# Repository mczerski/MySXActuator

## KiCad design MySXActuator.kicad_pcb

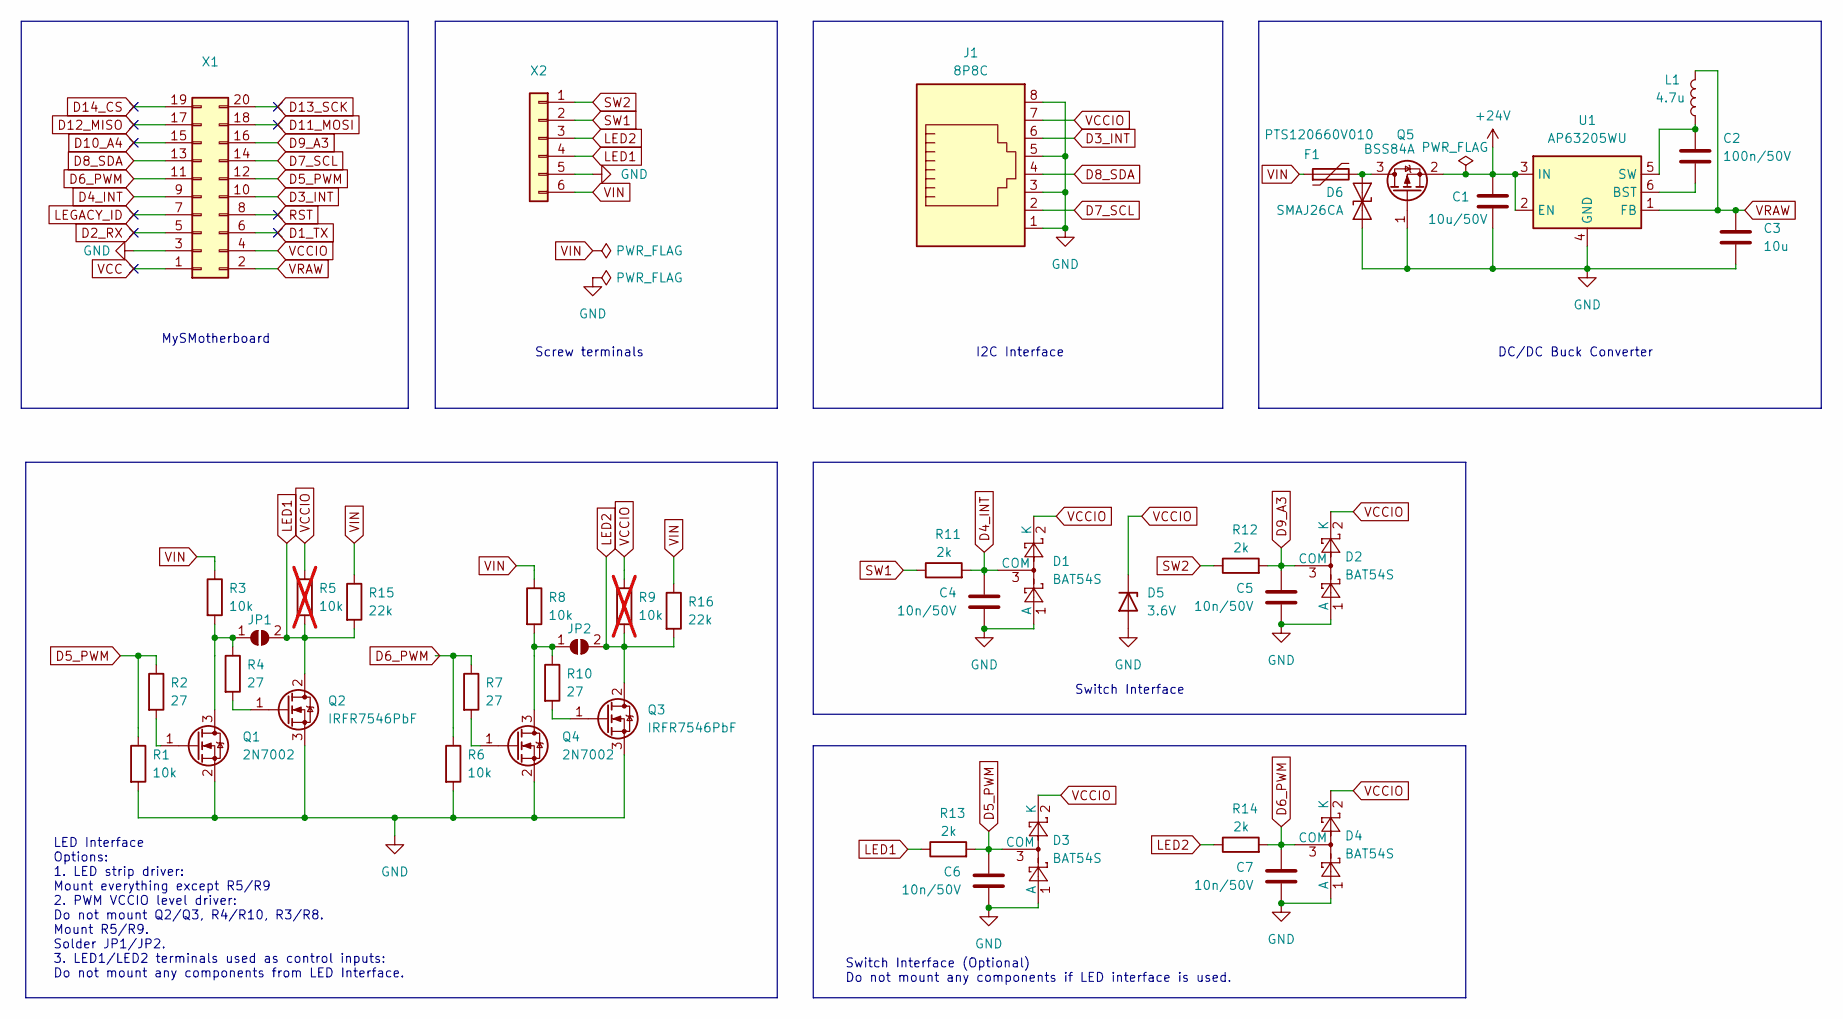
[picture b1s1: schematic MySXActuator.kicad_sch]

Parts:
C1: 10u/50V; C_1206_3216Metric
C2: 100n/50V; C_0402_1005Metric_Pad0.74x0.62mm_HandSolder
C3: 10u; C_1206_3216Metric
C4, C5, C6, C7: 10n/50V; C_0402_1005Metric
D1, D2, D3, D4: BAT54S; SOT-23
D5: 3.6V; D_MiniMELF
D6: SMAJ26CA; D_SMA
F1: PTS120660V010; Fuse_1206_3216Metric_Pad1.42x1.75mm_HandSolder
J1: 8P8C; AMPHENOL_54601-908WPLF
JP1, JP2: SolderJumper-2_P1.3mm_Open_RoundedPad1.0x1.5mm
L1: 4.7u; L_1210_3225Metric
Q1, Q4: 2N7002; SOT-23
Q2, Q3: IRFR7546PbF; TO-252-2
Q5: BSS84A; SOT-23
R1, R3, R6, R8: 10k; R_0603_1608Metric
R2, R4, R7, R10: 27; R_0603_1608Metric
R5, R9: 10k; R_0603_1608Metric; not fitted
R11, R12, R13, R14: 2k; R_0603_1608Metric
R15, R16: 22k; R_0603_1608Metric
U1: AP63205WU; TSOT-23-6
X1: FE10-2
X2: TerminalBlock_Phoenix_MKDS-1,5-6-5.08_1x06_P5.08mm_Horizont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

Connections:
+24V: C1.1, Q5.2 (S), U1.2 (EN), U1.3 (IN)
D1_TX: X1.6
D2_RX: X1.5
D3_INT: J1.6, X1.10
D4_INT: C4.1, D1.3 (COM), R11.2, X1.9
D5_PWM: C6.1, D3.3 (COM), R1.1, R2.1, R13.2, X1.12
D6_PWM: C7.1, D4.3 (COM), R6.1, R7.1, R14.2, X1.11
D7_SCL: J1.2, X1.14
D8_SDA: J1.4, X1.13
D9_A3: C5.1, D2.3 (COM), R12.2, X1.16
D10_A4: X1.15
D11_MOSI: X1.18
D12_MISO: X1.17
D13_SCK: X1.20
D14_CS: X1.19
GND: C1.2, C3.2, C4.2, C5.2, C6.2, C7.2, D1.1 (A), D2.1 (A), D3.1 (A), D4.1 (A), D5.2 (A), D6.1 (A1), J1.1, J1.3, J1.5, J1.8, Q1.2 (S), Q2.3 (S), Q3.3 (S), Q4.2 (S), Q5.1 (G), R1.2, R6.2, U1.4 (GND), X1.3, X2.5
LED1: JP1.2 (B), Q2.2 (D), R5.2, R13.1, R15.2, X2.4
LED2: JP2.2 (B), Q3.2 (D), R9.2, R14.1, R16.2, X2.3
LEGACY_ID: X1.7
unnamed: D6.2 (A2), F1.2, Q5.3 (D)
unnamed: JP1.1 (A), Q1.3 (D), R3.2, R4.1
unnamed: JP2.1 (A), Q4.3 (D), R8.2, R10.1
unnamed: Q1.1 (G), R2.2
unnamed: Q2.1 (G), R4.2
unnamed: Q3.1 (G), R10.2
unnamed: Q4.1 (G), R7.2
unnamed: C2.1, U1.6 (BST)
unnamed: C2.2, L1.1, U1.5 (SW)
RST: X1.8
SW1: R11.1, X2.2
SW2: R12.1, X2.1
VCC: X1.1
VCCIO: D1.2 (K), D2.2 (K), D3.2 (K), D4.2 (K), D5.1 (K), J1.7, R5.1, R9.1, X1.4
VIN: F1.1, R3.1, R8.1, R15.1, R16.1, X2.6
VRAW: C3.1, L1.2, U1.1 (FB), X1.2

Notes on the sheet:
I2C Interface
LED Interface Options: 1. LED strip driver: Mount everything except R5/R9 2. PWM VCCIO level driver: Do not mount Q2/Q3, R4/R10, R3/R8. Mount R5/R9. Solder JP1/JP2. 3. LED1/LED2 terminals used as control inputs: Do not mount any components from LED Interface.
Switch Interface
Switch Interface (Optional) Do not mount any components if LED interface is used.
DC/DC Buck Converter
Screw terminals
MySMotherboard

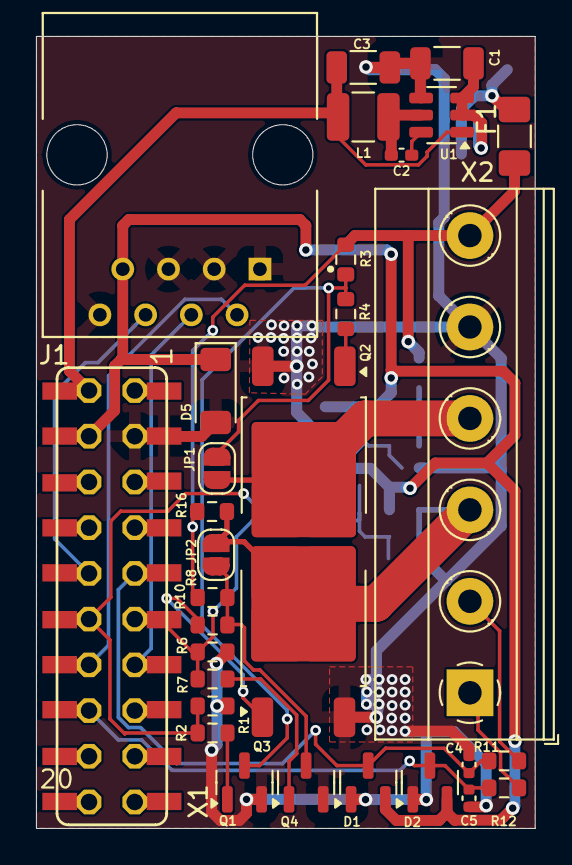
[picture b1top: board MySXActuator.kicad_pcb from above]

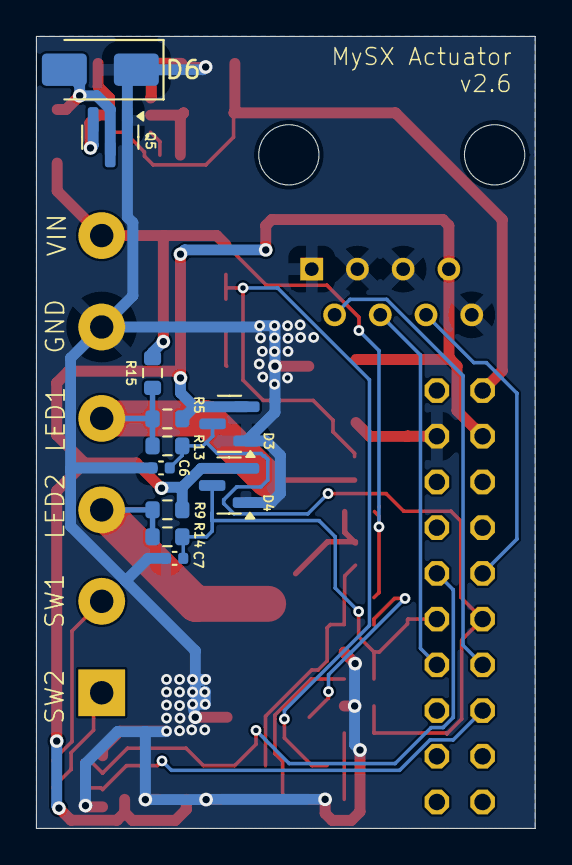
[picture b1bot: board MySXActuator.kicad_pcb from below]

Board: 2 copper layers, 27.7 x 44.0 mm, 42 parts (11 on the bottom side), 25 nets.

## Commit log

2019-03-27 initial commit, v1.0
2019-03-27 remove transistor value
2019-03-31 enlarge traces widths + add ldo
2019-04-03 add second dimmer
2019-04-04 fix stencil
2024-05-04 imported from eagle, ldo changed to buck converter
2024-05-05 change C2 footprint from 0201 to 0402
2024-05-05 add screenshot of the board
2024-05-25 refactor schematic to use kicad native symbols and footprints
2024-06-08 add reverse polarity protection and overvoltage protection for input pins
2024-07-26 add schematic export
2024-07-27 update schematic
    - add zener diode to protect high positive voltage on inputs
    - add anoter 2 input sections as alternative to led drivers
    - add add rj45 socket for i2c interface
2024-07-27 update PCB after schematic changes
2024-09-18 Add removed buck converter
    - previously removed buck converter is needed to not require power from
    RS485 line
    - position RJ45 connector closer to center of the board to allow use
    straigth connector (facing up)
    - replace THT power transistors with SMT power transistors
2026-06-11 add input voltage transient protection
2026-06-14 add resistors to prevent led glowing when turned off
